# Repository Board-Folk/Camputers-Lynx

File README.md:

# Camputers Lynx 48/96/128/192

Repository for the 2023 Board Folk Recreation of the main boards of the Camputers Lynx 48/96K and 128K (192K) computers.

** Work in progress **

The original 48/96K system can be found in the Lynx 96 folder. The system needs the 16K RAM expansion board to operate (see Expansions folder). This was originally supplied as a 48K system (16K+16K+16K) then retrofitted after market by the manufacturer to be a 96K system (64K+16K+16K). It's the same board.

The second system that started production, the 128, is in the Lynx 128 folder. This system in production had presets to 128K, though could have 192K fitted. The 128K preset board (untested) can be found here. There's also a tested board without presets which can be jumpered to use 192K and can be found in the archive subfolder off here. 

Though the board without presets and appropriate jumpers set has been tested, and seems to work fine, any attempts for it to use 192K failed. It's perceived that it might need a different set of ROMs that we don't have. We're not experts and will have to defer to the Lynx community on that. See the info folder in there for jumper settings.

Be wary, the two systems aren't 100% compatible. The most compatible system is a Lynx 48 for games. The Lynx 128, compatibility was much reduced, though CP/M (untested) was an option with ROM replacements and a disc interface.

Kicad files, Gerbers and iBOMs in their respective folders for now. More information, pictures, etc may follow in time.

Keyboard boards can be found off the Expansions sub-folder in Lynx 96.

To note, we had terrible problems with RCA brand CD4538BE building these, please avoid.

## Credit

PCB layouts by Rob Taylor @peepouk. Schematics recreated by Ian Cudlip @grandoldian.

## Thanks

  * The rest of the Board Folk Team

## Legal

As the product of this project is a replica of a proprietary product, the the author makes no claim of copyright to the schematics nor PCB layouts and releases these into the public domain, solely for the purposes of study and historical preservation.

You are free to produce PCBs based on this project's designs at your own risk and without limitation, for your own use or for sale and/or repair at a reasonable price. Attribution is appreciated. The authors are not obliged to provide support of any kind. 

Under no circumstances will the authors be held responsible or liable in any way for losses, damages or costs resulting from the use of the information and/or resources of this project. 

The resources are provided "as-is" without warranty of any kind, either expressed or implied, including, but not limited to, the implied warranties of merchantability and fitness for a particular purpose.

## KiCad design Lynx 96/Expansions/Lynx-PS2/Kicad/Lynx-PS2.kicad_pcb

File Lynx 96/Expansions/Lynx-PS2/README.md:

# Lynx PS2

ATMega328 based PS/2 Keyboard Adapter for the Camputers Lynx. Arduino code and exported binaries in the Arduino folder.

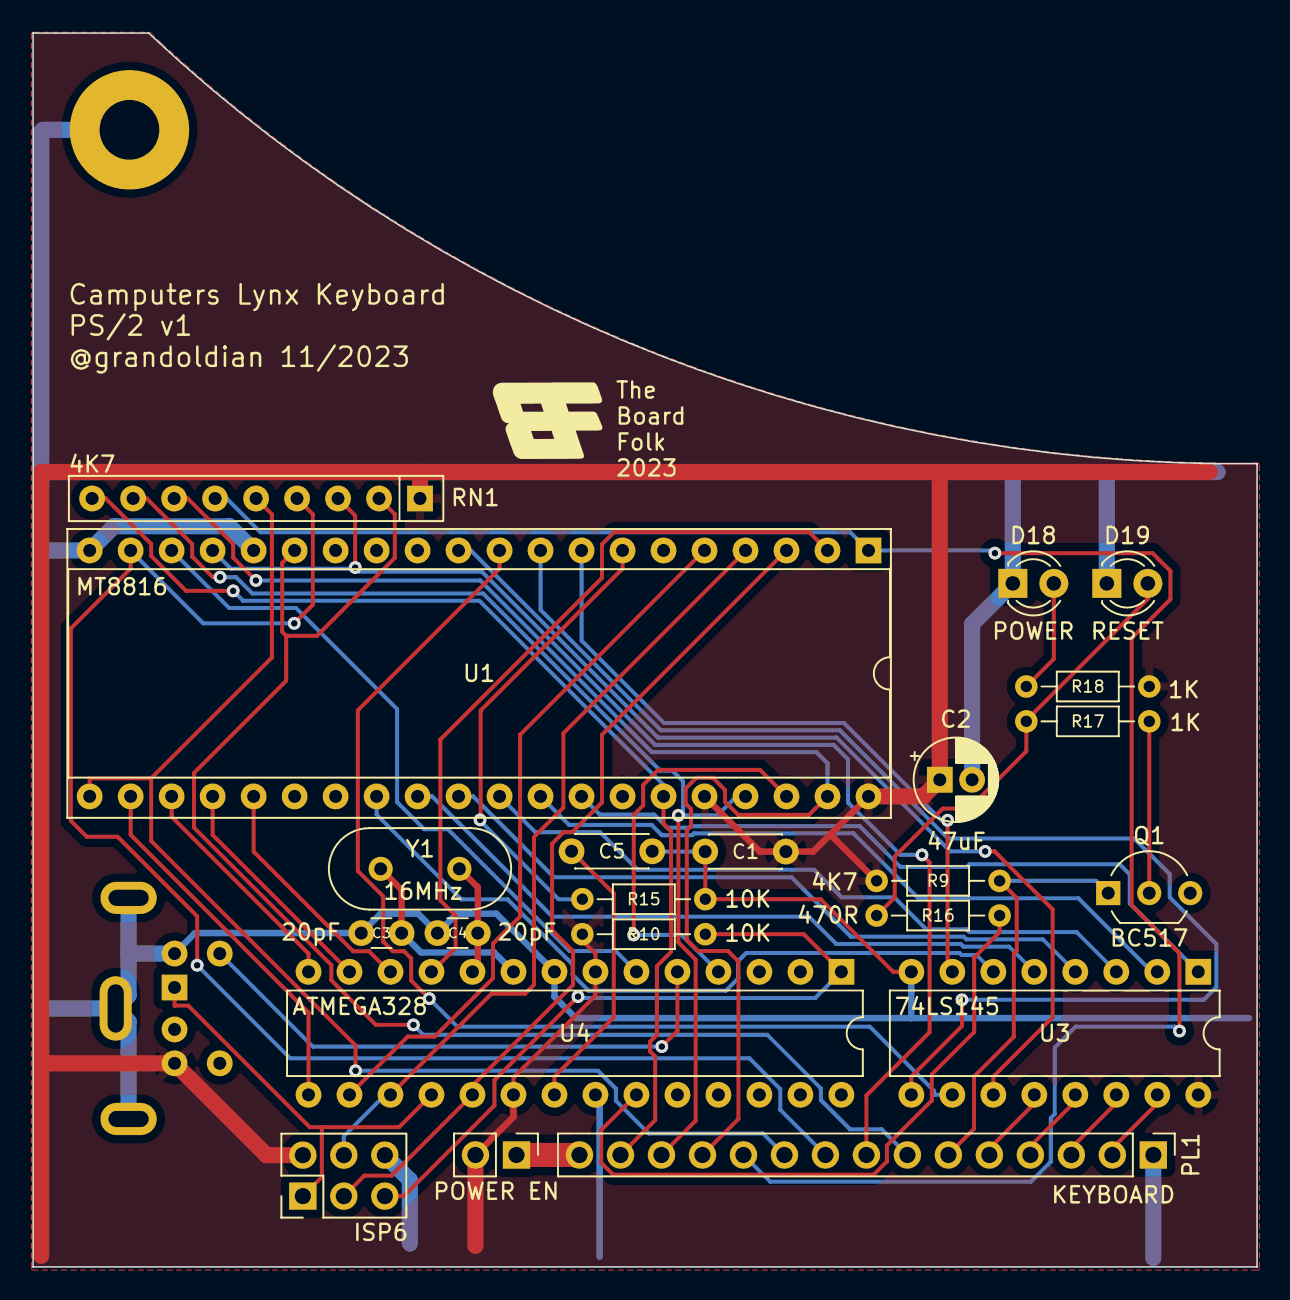
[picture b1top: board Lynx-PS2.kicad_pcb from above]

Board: 2 copper layers, 75.8 x 76.5 mm, 25 parts (1 on the bottom side), 47 nets.

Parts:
C1: 47nF; C_Disc_D4.3mm_W1.9mm_P5.00mm
C2: 47uF; CP_Radial_D5.0mm_P2.00mm
C3, C4: 20pF; C_Disc_D3.0mm_W1.6mm_P2.50mm
C5: 100nF; C_Disc_D4.3mm_W1.9mm_P5.00mm
D18: POWER; LED_D3.0mm
D19: RESET; LED_D3.0mm
G1: Board Folk Logo; BF8
H1: Hole; MountingHole_3.7mm_Pad
J1: POWER EN; PinHeader_1x02_P2.54mm_Vertical
J3: PS/2; Connector_Mini-DIN_Female_6Pin_2rows
J800: ISP6; PinHeader_2x03_P2.54mm_Vertical
PL1: KEYBOARD; PinHeader_1x15_P2.54mm_Vertical
Q1: BC517; TO-92_Inline_Wide
R9: 4K7; R_Axial_DIN0204_L3.6mm_D1.6mm_P7.62mm_Horizontal
R10, R15: 10K; R_Axial_DIN0204_L3.6mm_D1.6mm_P7.62mm_Horizontal
R16: 470R; R_Axial_DIN0204_L3.6mm_D1.6mm_P7.62mm_Horizontal
R17, R18: 1K; R_Axial_DIN0204_L3.6mm_D1.6mm_P7.62mm_Horizontal
RN1: 4K7; R_Array_SIP9
U1: MT8816; DIP-40_W15.24mm_Socket
U3: 74LS145; DIP-16_W7.62mm
U4: ATMEGA328; DIP-28_W7.62mm
Y1: 16MHz; Crystal_HC49-U_Vertical

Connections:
!RST: PL1.6, Q1.1 (C), R9.1
+5V: C1.2, C2.1, J1.2, J3.4, J800.2, R9.2, R10.1, R18.2, RN1.1 (common), U1.36, U1.40, U3.16 (VCC), U4.7 (VCC), U4.20 (AVCC)
/KBA0: PL1.2, U3.15 (A)
/KBA1: PL1.3, U3.14 (B)
/KBA2: PL1.4, U3.13 (C)
/KBA3: PL1.5, U3.12 (D)
ADMISO: J3.1, J800.1, U4.18 (PB4)
ADMOSI: J800.4, U1.4, U4.17 (PB3)
ADRESET: J800.5, R10.2, U4.1 (PC6)
ADSCK: J800.3, U1.3, U4.19 (PB5)
AX0: U1.5, U4.16 (PB2)
AX1: U1.22, U4.15 (PB1)
AX2: U1.23, U4.14 (PB0)
AY0: U1.24, U4.13 (PD7)
AY1: U1.25, U4.12 (PD6)
AY2: U1.2, U4.11 (PD5)
BREAK: R16.2, U4.23 (PC0)
COL0: U1.33, U3.1 (~Q0)
COL1: U1.32, U3.2 (~Q1)
COL2: U1.31, U3.3 (~Q2)
COL3: U1.30, U3.4 (~Q3)
COL4: U1.29, U3.5 (~Q4)
COL5: U1.28, U3.6 (~Q5)
COL6: U1.8, U3.7 (~Q6)
COL7: U1.9, U3.9 (~Q7)
COL8: U1.10, U3.10 (~Q8)
COL9: U1.11, U3.11 (~Q9)
FLOAT: R15.1, U1.7
GND: C1.1, C2.2, C3.2, C4.2, C5.2, D18.1 (K), D19.1 (K), H1.1, J3.3, J3.7, J800.6, PL1.1, Q1.3 (E), R15.2, U1.16, U1.20, U3.8 (GND), U4.8 (GND), U4.22 (GND)
MTDATA: U1.38, U4.4 (PD2)
MTSTROBE: U1.18, U4.6 (PD4)
unnamed: D18.2 (A), R18.1
unnamed: D19.2 (A), R16.1, R17.2
unnamed: J1.1, PL1.15
unnamed: Q1.2 (B), R17.1
unnamed: C5.1, U4.21 (AREF)
unnamed: C3.1, U4.9 (PB6), Y1.1
unnamed: C4.1, U4.10 (PB7), Y1.2
PS2-CLK: J3.5, U4.5 (PD3)
ROW0: PL1.14, RN1.9 (R8), U1.35
ROW1: PL1.13, RN1.8 (R7), U1.37
ROW2: PL1.12, RN1.7 (R6), U1.39
ROW3: PL1.11, RN1.6 (R5), U1.1
ROW4: PL1.10, RN1.5 (R4), U1.21
ROW5: PL1.9, RN1.4 (R3), U1.19
ROW6: PL1.8, RN1.3 (R2), U1.17
ROW7: PL1.7, RN1.2 (R1), U1.15

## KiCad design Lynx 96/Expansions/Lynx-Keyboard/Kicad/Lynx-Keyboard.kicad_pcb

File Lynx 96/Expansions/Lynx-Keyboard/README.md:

# Lynx Keyboard

Lynx MX Keyswitch Compatible Keyboard

Thanks to Graham Thornton for measurements. We've still not been able to try see if it fits an original case though.

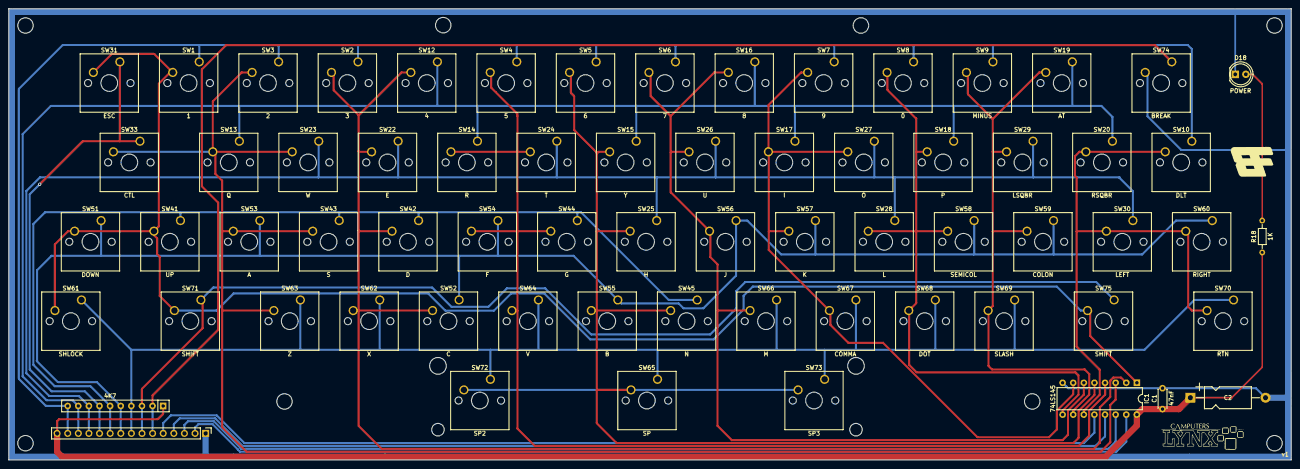
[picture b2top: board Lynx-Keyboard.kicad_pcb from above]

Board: 2 copper layers, 307.0 x 108.0 mm, 78 parts (1 on the bottom side), 26 nets.

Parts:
C1: 47nF; C_Disc_D4.3mm_W1.9mm_P5.00mm
C2: 47uF; CP_Axial_L11.0mm_D5.0mm_P18.00mm_Horizontal
D18: POWER; LED_D5.0mm
G1: Board Folk Logo; BF12
G2: Camputer Lynx Logo; CLLogo
G3: Board Folk QR; bf_qr14
H1, H2, H3, H4, H5, H6, H7, H8: Hole; MountingHole_3.7mm
IC1: 74LS145; DIP-16_W7.62mm
PL1: KEYBOARD; PinHeader_1x15_P2.54mm_Vertical
R18: 1K; R_Axial_DIN0204_L3.6mm_D1.6mm_P7.62mm_Horizontal
RN1: 4K7; R_Array_SIP10
SW1: 1; SW_Cherry_MX_1.00u_PCB
SW2: 3; SW_Cherry_MX_1.00u_PCB
SW3: 2; SW_Cherry_MX_1.00u_PCB
SW4: 5; SW_Cherry_MX_1.00u_PCB
SW5: 6; SW_Cherry_MX_1.00u_PCB
SW6: 7; SW_Cherry_MX_1.00u_PCB
SW7: 9; SW_Cherry_MX_1.00u_PCB
SW8: 0; SW_Cherry_MX_1.00u_PCB
SW9: MINUS; SW_Cherry_MX_1.00u_PCB
SW10: DLT; SW_Cherry_MX_1.00u_PCB
SW12: 4; SW_Cherry_MX_1.00u_PCB
SW13: Q; SW_Cherry_MX_1.00u_PCB
SW14: R; SW_Cherry_MX_1.00u_PCB
SW15: Y; SW_Cherry_MX_1.00u_PCB
SW16: 8; SW_Cherry_MX_1.00u_PCB
SW17: I; SW_Cherry_MX_1.00u_PCB
SW18: P; SW_Cherry_MX_1.00u_PCB
SW19: AT; SW_Cherry_MX_1.00u_PCB
SW20: RSQBR; SW_Cherry_MX_1.00u_PCB
SW22: E; SW_Cherry_MX_1.00u_PCB
SW23: W; SW_Cherry_MX_1.00u_PCB
SW24: T; SW_Cherry_MX_1.00u_PCB
SW25: H; SW_Cherry_MX_1.00u_PCB
SW26: U; SW_Cherry_MX_1.00u_PCB
SW27: O; SW_Cherry_MX_1.00u_PCB
SW28: L; SW_Cherry_MX_1.00u_PCB
SW29: LSQBR; SW_Cherry_MX_1.00u_PCB
SW30: LEFT; SW_Cherry_MX_1.00u_PCB
SW31: ESC; SW_Cherry_MX_1.00u_PCB
SW33: CTL; SW_Cherry_MX_1.50u_PCB
SW41: UP; SW_Cherry_MX_1.00u_PCB
SW42: D; SW_Cherry_MX_1.00u_PCB
SW43: S; SW_Cherry_MX_1.00u_PCB
SW44: G; SW_Cherry_MX_1.00u_PCB
SW45: N; SW_Cherry_MX_1.00u_PCB
SW51: DOWN; SW_Cherry_MX_1.00u_PCB
SW52: C; SW_Cherry_MX_1.00u_PCB
SW53: A; SW_Cherry_MX_1.00u_PCB
SW54: F; SW_Cherry_MX_1.00u_PCB
SW55: B; SW_Cherry_MX_1.00u_PCB
SW56: J; SW_Cherry_MX_1.00u_PCB
SW57: K; SW_Cherry_MX_1.00u_PCB
SW58: SEMICOL; SW_Cherry_MX_1.00u_PCB
SW59: COLON; SW_Cherry_MX_1.00u_PCB
SW60: RIGHT; SW_Cherry_MX_1.00u_PCB
SW61: SHLOCK; SW_Cherry_MX_1.50u_PCB
SW62: X; SW_Cherry_MX_1.00u_PCB
SW63: Z; SW_Cherry_MX_1.00u_PCB
SW64: V; SW_Cherry_MX_1.00u_PCB
SW65: SP; SW_Cherry_MX_1.00u_PCB
SW66: M; SW_Cherry_MX_1.00u_PCB
SW67: COMMA; SW_Cherry_MX_1.00u_PCB
SW68: DOT; SW_Cherry_MX_1.00u_PCB
SW69: SLASH; SW_Cherry_MX_1.00u_PCB
SW70: RTN; SW_Cherry_MX_1.50u_PCB
SW71, SW75: SHIFT; SW_Cherry_MX_1.50u_PCB
SW72: SP2; SW_Cherry_MX_1.00u_PCB
SW73: SP3; SW_Cherry_MX_1.00u_PCB
SW74: BREAK; SW_Cherry_MX_1.50u_PCB

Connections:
!RST: PL1.6, RN1.2 (R1), SW74.1 (A)
+5V: C1.2, C2.1, IC1.16 (VCC), PL1.15, R18.2, RN1.1 (common)
/KBA0: IC1.15 (A), PL1.2
/KBA1: IC1.14 (B), PL1.3
/KBA2: IC1.13 (C), PL1.4
/KBA3: IC1.12 (D), PL1.5
COL0: IC1.1 (~Q0), SW1.2 (B), SW31.2 (B), SW41.2 (B), SW51.2 (B), SW61.2 (B), SW71.2 (B), SW75.2 (B)
COL1: IC1.2 (~Q1), SW2.2 (B), SW12.2 (B), SW22.2 (B), SW42.2 (B), SW52.2 (B), SW62.2 (B)
COL2: IC1.3 (~Q2), SW3.2 (B), SW13.2 (B), SW23.2 (B), SW33.2 (B), SW43.2 (B), SW53.2 (B), SW63.2 (B)
COL3: IC1.4 (~Q3), SW4.2 (B), SW14.2 (B), SW24.2 (B), SW44.2 (B), SW54.2 (B), SW64.2 (B)
COL4: IC1.5 (~Q4), SW5.2 (B), SW15.2 (B), SW25.2 (B), SW45.2 (B), SW55.2 (B), SW65.2 (B), SW72.2 (B), SW73.2 (B)
COL5: IC1.6 (~Q5), SW6.2 (B), SW16.2 (B), SW26.2 (B), SW56.2 (B), SW66.2 (B)
COL6: IC1.7 (~Q6), SW7.2 (B), SW17.2 (B), SW27.2 (B), SW57.2 (B), SW67.2 (B)
COL7: IC1.9 (~Q7), SW8.2 (B), SW18.2 (B), SW28.2 (B), SW58.2 (B), SW68.2 (B)
COL8: IC1.10 (~Q8), SW9.2 (B), SW19.2 (B), SW29.2 (B), SW59.2 (B), SW69.2 (B)
COL9: IC1.11 (~Q9), SW10.2 (B), SW20.2 (B), SW30.2 (B), SW60.2 (B), SW70.2 (B)
GND: C1.1, C2.2, D18.1 (K), IC1.8 (GND), PL1.1, SW74.2 (B)
unnamed: D18.2 (A), R18.1
ROW0: PL1.14, RN1.10 (R9), SW1.1 (A), SW2.1 (A), SW3.1 (A), SW4.1 (A), SW5.1 (A), SW6.1 (A), SW7.1 (A), SW8.1 (A), SW9.1 (A), SW10.1 (A)
ROW1: PL1.13, RN1.9 (R8), SW12.1 (A), SW13.1 (A), SW14.1 (A), SW15.1 (A), SW16.1 (A), SW17.1 (A), SW18.1 (A), SW19.1 (A), SW20.1 (A)
ROW2: PL1.12, RN1.8 (R7), SW22.1 (A), SW23.1 (A), SW24.1 (A), SW25.1 (A), SW26.1 (A), SW27.1 (A), SW28.1 (A), SW29.1 (A), SW30.1 (A)
ROW3: PL1.11, RN1.7 (R6), SW31.1 (A), SW33.1 (A)
ROW4: PL1.10, RN1.6 (R5), SW41.1 (A), SW42.1 (A), SW43.1 (A), SW44.1 (A), SW45.1 (A)
ROW5: PL1.9, RN1.5 (R4), SW51.1 (A), SW52.1 (A), SW53.1 (A), SW54.1 (A), SW55.1 (A), SW56.1 (A), SW57.1 (A), SW58.1 (A), SW59.1 (A), SW60.1 (A)
ROW6: PL1.8, RN1.4 (R3), SW61.1 (A), SW62.1 (A), SW63.1 (A), SW64.1 (A), SW65.1 (A), SW66.1 (A), SW67.1 (A), SW68.1 (A), SW69.1 (A), SW70.1 (A), SW72.1 (A), SW73.1 (A)
ROW7: PL1.7, RN1.3 (R2), SW71.1 (A), SW75.1 (A)

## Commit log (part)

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2025-07-15 Rebase
2025-07-15 Jumper Settings
2025-09-27 Update 48/98 Jumper
